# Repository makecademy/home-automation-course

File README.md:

# home-automation-course
Code for the Building Home Automation Systems video course

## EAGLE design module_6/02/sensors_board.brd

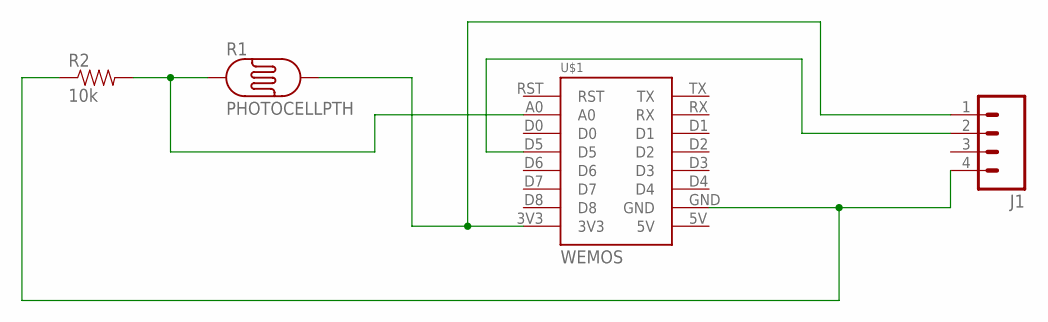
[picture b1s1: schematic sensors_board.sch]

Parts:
J1: M04PTH; 1X04
R1: PHOTOCELLPTH; PHOTOCELL
R2: 10k; AXIAL-0.3
U$1: WEMOS

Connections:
unnamed: J1.4, R2.P$1 (1), U$1.GND
unnamed: J1.1, R1.2, U$1.3V3
unnamed: J1.2, U$1.D5
unnamed: R1.1, R2.P$2 (2), U$1.A0

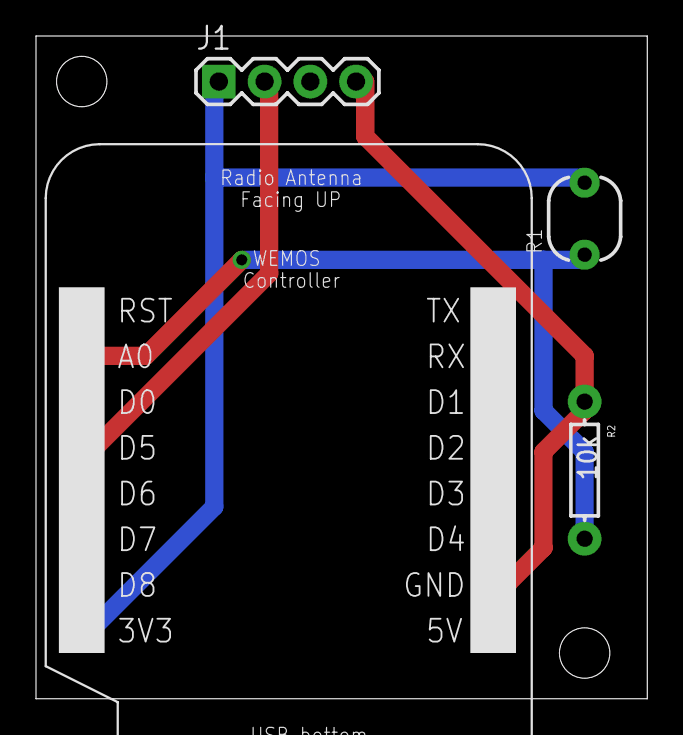
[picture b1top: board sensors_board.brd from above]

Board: 2 copper layers, 34.0 x 36.8 mm, 4 parts (0 on the bottom side), 4 nets.

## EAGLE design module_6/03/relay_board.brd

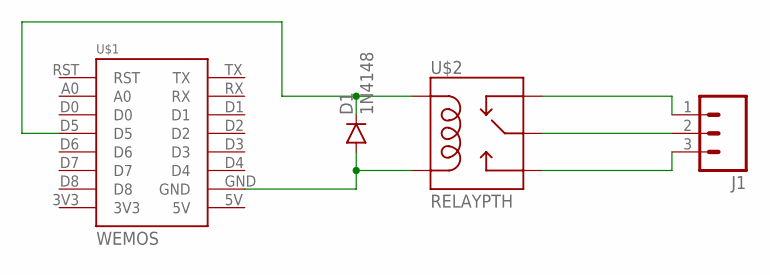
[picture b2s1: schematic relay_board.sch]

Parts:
D1: 1N4148; DIODE-1N4148
J1: M03SCREW; SCREWTERMINAL-3.5MM-3
U$1: WEMOS
U$2: RELAYPTH; RELAY-G5Q

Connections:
unnamed: D1.A, U$1.GND, U$2.1 (COIL2)
unnamed: D1.C, U$1.D5, U$2.5 (COIL1)
unnamed: J1.1, U$2.4 (NC)
unnamed: J1.2, U$2.2 (MAIN)
unnamed: J1.3, U$2.3 (NO)

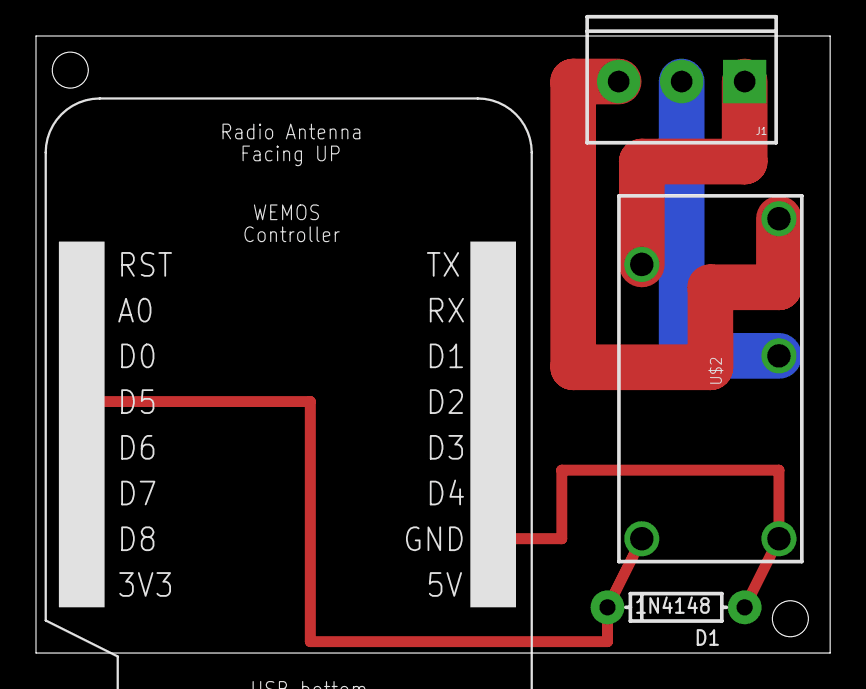
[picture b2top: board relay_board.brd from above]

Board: 2 copper layers, 44.1 x 34.3 mm, 4 parts (0 on the bottom side), 5 nets.

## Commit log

2016-09-13 added module 3 files
2016-09-13 added all files chapter 3
2016-09-13 code update
2016-09-19 module 4 code added
2016-09-19 added video 3 module 4
2016-09-25 added module 5
2016-09-25 fix dropbox scrit
2016-09-25 fix dropbox script
2016-09-26 added more chapter 5
2016-10-03 module 5 added
2016-10-10 added chapter 6
2016-10-18 added end of module 6
2016-11-14 adding module 2

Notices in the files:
parts and their libraries:
SparkFun-Connectors: Licensing: Creative Commons ShareAlike 4.0 International - https://creativecommons.org/licenses/by-sa/4.0
